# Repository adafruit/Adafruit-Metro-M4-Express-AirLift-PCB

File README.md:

## Adafruit Metro M4 Express AirLift (WiFi) - Lite PCB

<a href="http://www.adafruit.com/products/4000"><br/>
Click here to purchase one from the Adafruit shop</a>

PCB files for the Adafruit Metro M4 Express AirLift (WiFi) - Lite. 

Format is EagleCAD schematic and board layout
* https://www.adafruit.com/product/4000

### Description

Give your next project a lift with _AirLift_ - our witty name for the ESP32 co-processor that graces this Metro M4. You already know about the **Adafruit Metro M4** featuring the **Microchip ATSAMD51**, with it's 120MHz Cortex M4 with floating point support. With a train-load of FLASH and RAM, your code will be fast and roomy. And what better way to improve it than to add wireless? Now cooked in directly on board, you get a certified WiFi module that can handle all your TLS and socket needs, it even has root certificates pre-loaded.

This Metro is the same size as the others, and is compatible with all our shields. It's got analog pins where you expect, and SPI/UART/I2C hardware support in the same spot as the Metro 328 and M0. But! It's powered with an ATSAMD51J19:
 * Cortex M4 core running at **120 MHz**
 * [Floating point support with Cortex M4 DSP instructions](https://developer.arm.com/technologies/dsp/dsp-for-cortex-m)
 * **512 KB** flash, **192 KB** RAM
 * 32-bit, 3.3V logic and power
 * Dual 1 MSPS DAC (A0 and A1)
 * Dual 1 MSPS ADC (8 analog pins)
 * 6 x hardware SERCOM (I2C, SPI or UART)
 * 22 x PWM outputs
 * Stereo I2S input/output with MCK pin
 * 10-bit Parallel capture controller (for camera/video in)
 * Built in crypto engines with AES (256 bit), true RNG, Pubkey controller
 * 64 QFN

Pretty good start right? So we put this chip on a PCB with all these nice extras:
 * **Power the METRO M4** with 7-9V polarity protected DC or the micro USB connector to any 5V USB source. The 2.1mm DC jack has an on/off switch next to it so you can turn off your setup easily. The METRO will automagically switch between USB and DC.
 * **METRO has 25 GPIO** pins, 8 of which are analog in, and two of which is a true analog out. There's a hardware SPI port, hardware I2C port and hardware UART. Logic level is 3.3V
 * **Native USB**, there's no need for a hardware USB to Serial converter as the Metro M4 has built in USB support. When used to act like a serial device, the USB interface can be used by any computer to listen/send data to the METRO, and can also be used to launch and update code via the bootloader. It can also act like an HID keyboard or mouse.
 * **AirLift WiFi Co-processor**, with TLS/SSL support, plenty of RAM for sockets, communication is over SPI and has Arduino and CircuitPython libraries ready to go for fast wireless integration.
 * **Four indicator LEDs and one NeoPixel**, on the back edge of the PCB, for easy debugging. One green power LED, two RX/TX LEDs for data being sent over USB, and a red LED connected. Next to the reset button there is an RGB NeoPixel that can be used for any purpose.
 * **2 MB QSPI Flash** storage chip is included on board. You can use the SPI Flash storage like a very tiny hard drive. When used in Circuit Python, the 2 MB flash acts as storage for all your scripts, libraries and files. When used in Arduino, you can read/write files to it, like a little datalogger or SD card, and then with our helper program, access the files over USB.
 * **Easy reprogramming**, comes pre-loaded with the [UF2 bootloader](https://learn.adafruit.com/adafruit-metro-m0-express-designed-for-circuitpython/uf2-bootloader), which looks like a USB storage key. Simply drag firmware on to program, no special tools or drivers needed! It can be used to load up CircuitPython or Arduino IDE (it is bossa v1.8 compatible)
We have a working Arduino board support package, with lots of stuff working, but our primary target for this board is CircuitPython - with 120 MHz, and 192KB of RAM CircuitPython runs really well on this chip! CircuitPython's built in support for JSON parsing plus our requests compatible library makes it incredibly easy to build secure IoT projects in just a few minutes.

So what are you waiting for? Pick up a Metro M4 AirLift today and be amazed at how easy and fast it is to get started with IoT projects using CircuitPython!

### License

Adafruit invests time and resources providing this open source design, please support Adafruit and open-source hardware by purchasing products from [Adafruit](https://www.adafruit.com)!

Designed by Limor Fried/Ladyada for Adafruit Industries.

Creative Commons Attribution/Share-Alike, all text above must be included in any redistribution. 
See license.txt for additional details.

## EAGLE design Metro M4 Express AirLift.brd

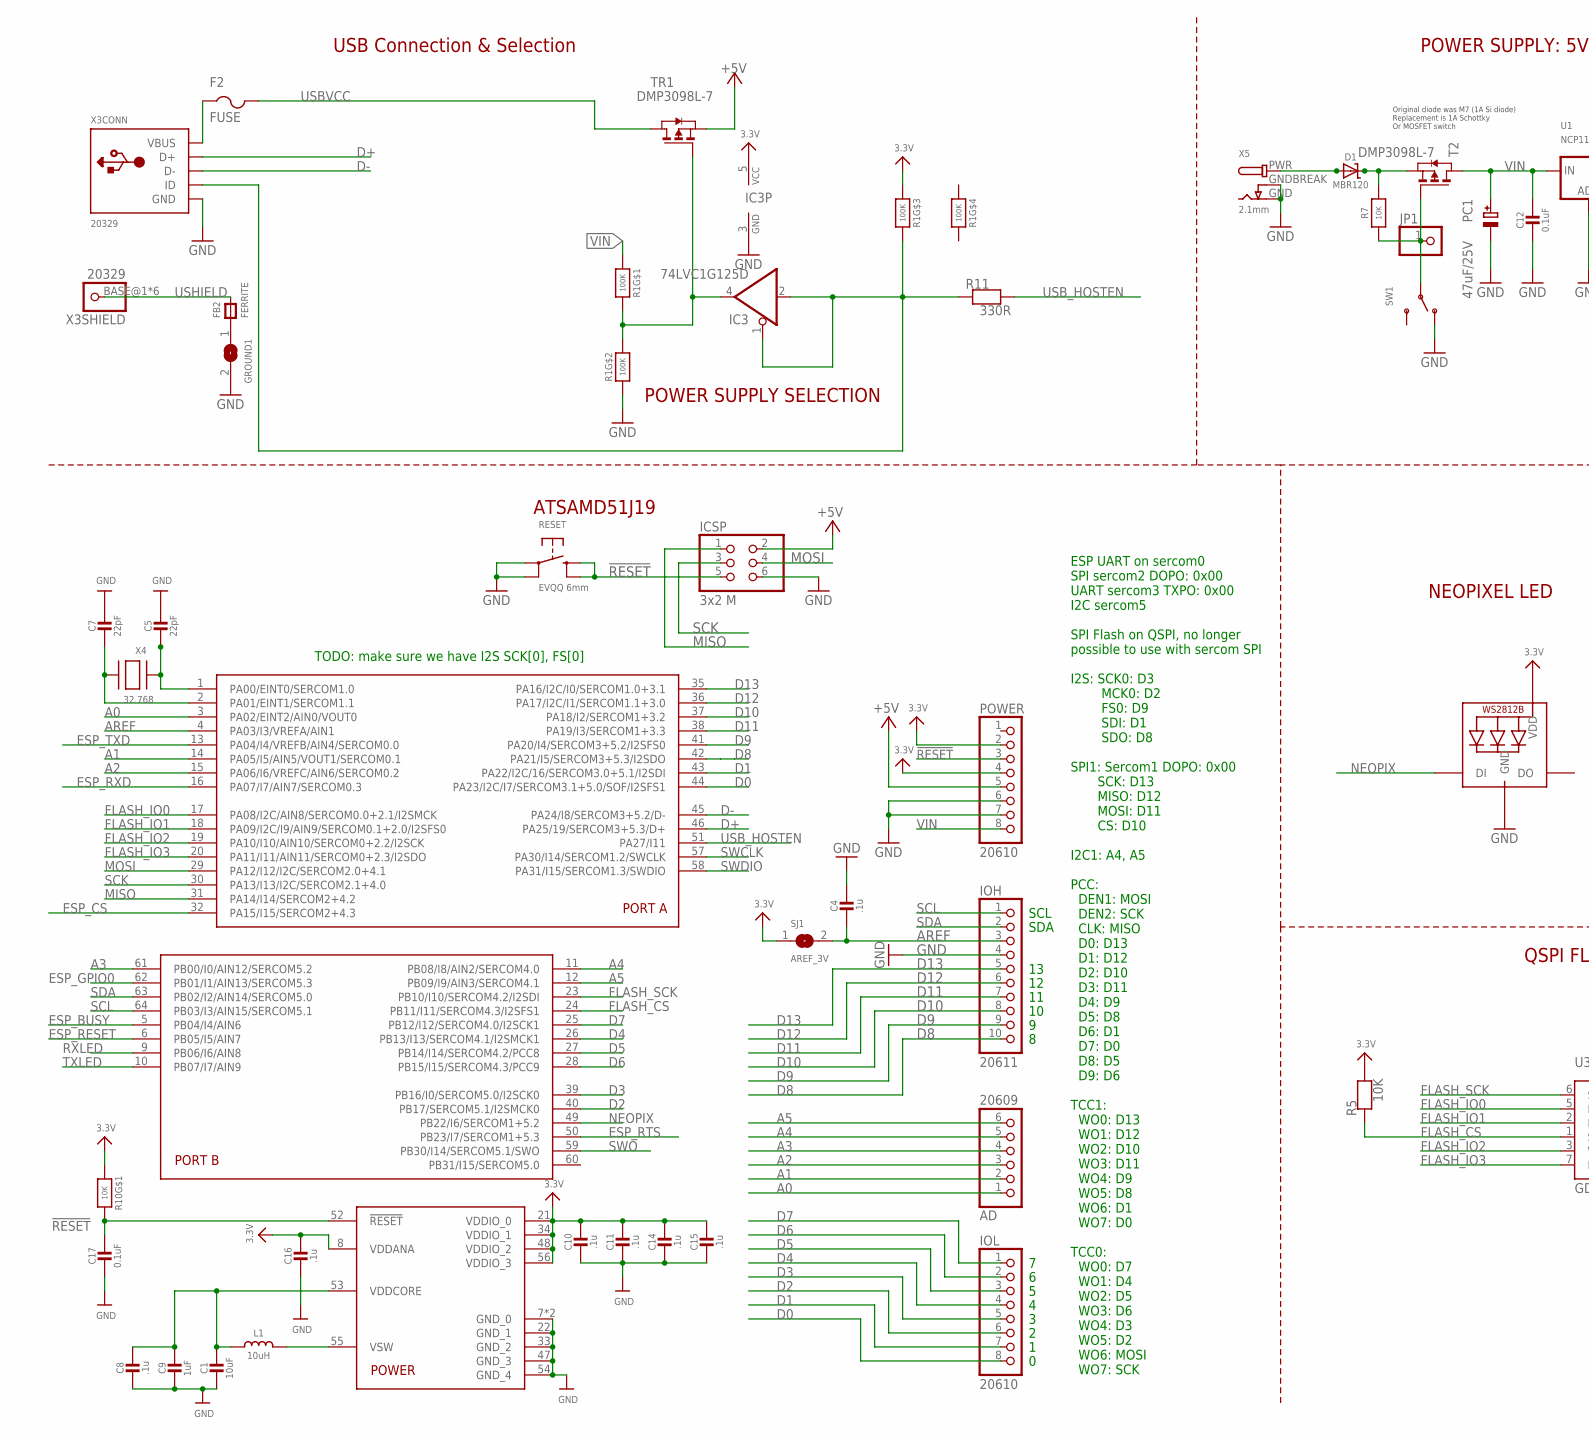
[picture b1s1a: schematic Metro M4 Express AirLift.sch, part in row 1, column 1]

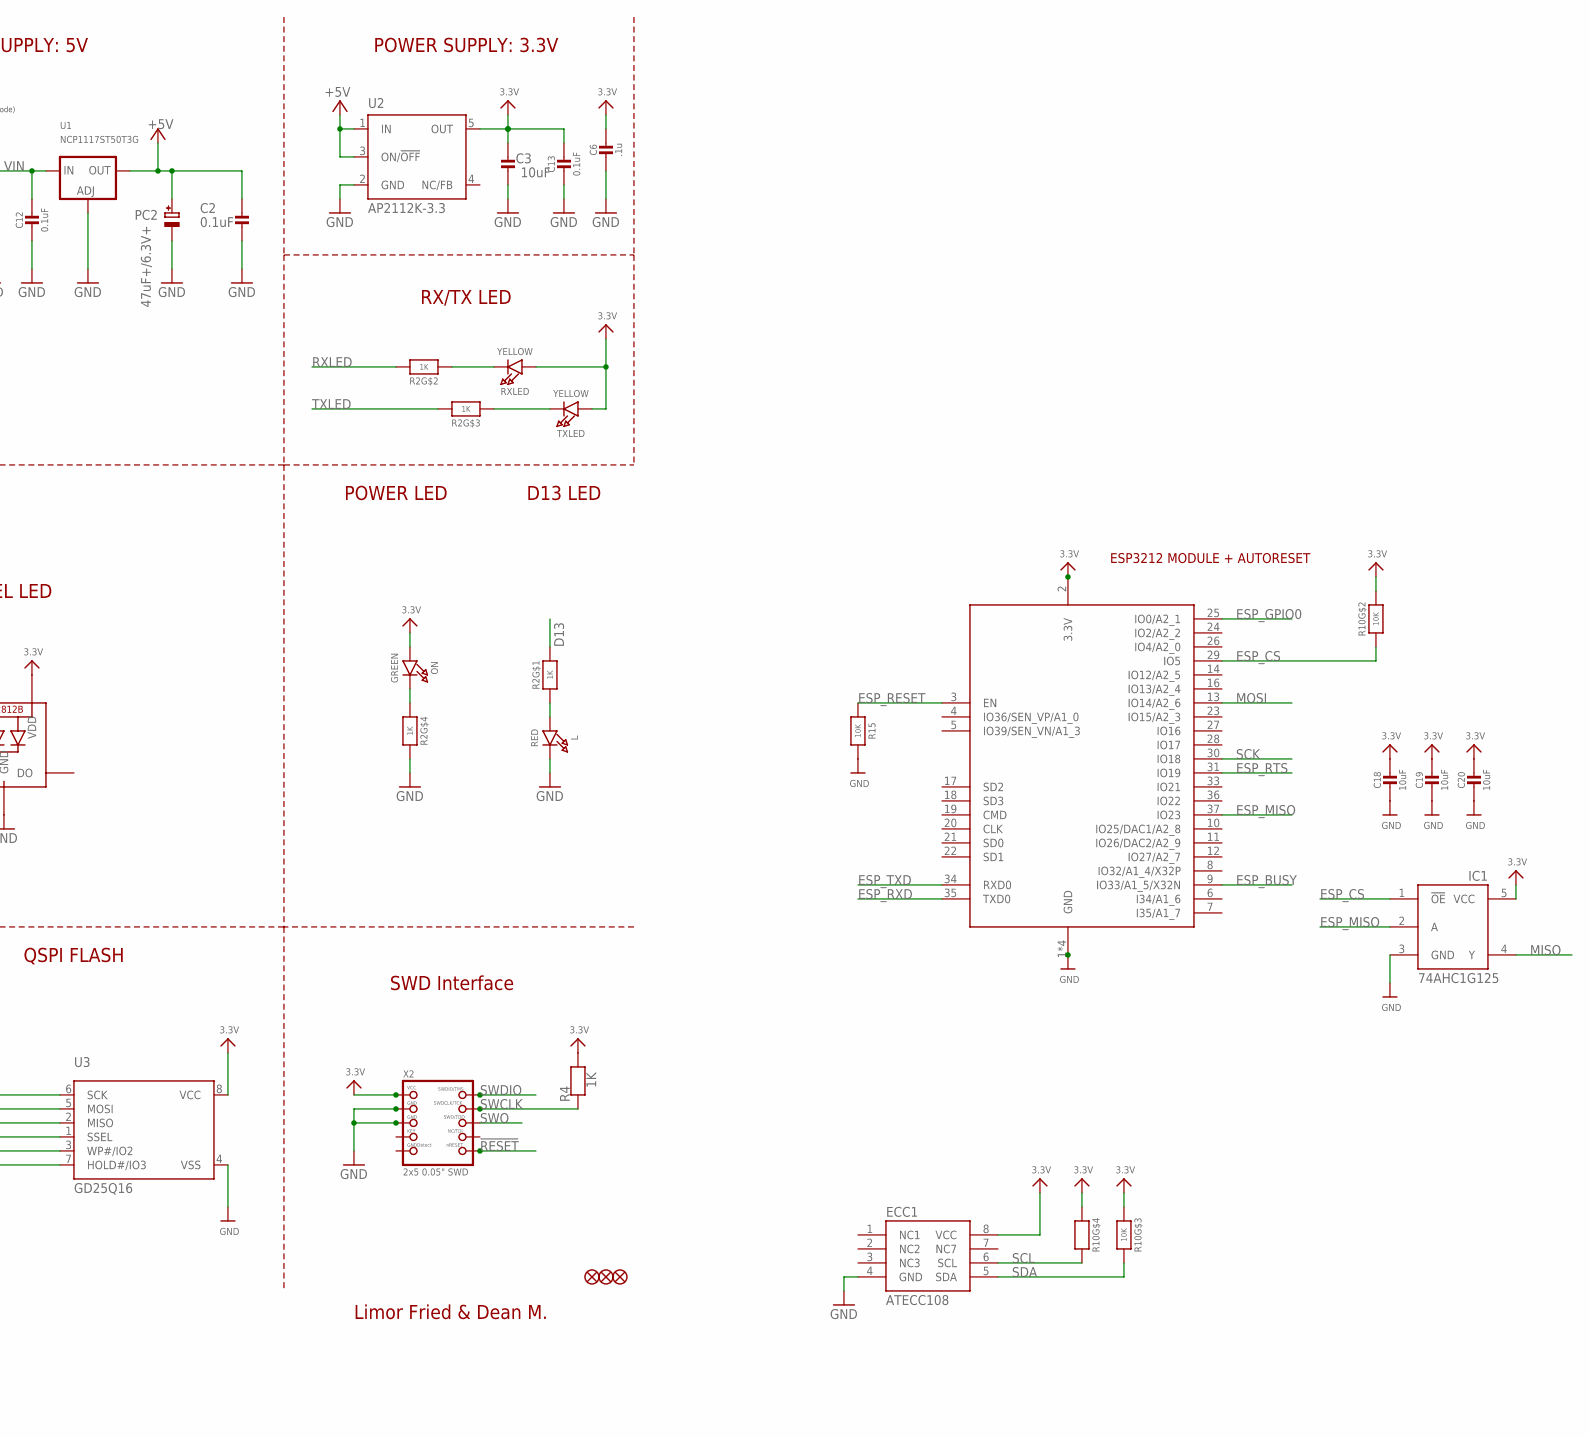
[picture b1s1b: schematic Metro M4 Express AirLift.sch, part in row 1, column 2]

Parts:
AD: 20609; 1X06_OVALWAVE
C1, C3, C18, C19, C20: 10uF; 0805-NO
C2: 0.1uF; 0805-NO
C4, C6, C8, C10, C11, C14, C15, C16: .1u; 0603-NO
C5, C7: 22pF; 0603-NO
C9: 1uF; 0603-NO
C12, C13, C17: 0.1uF; 0603-NO
D1: MBR120; SOD-123
ECC1: ATECC108; SOIC8
F2: FUSE; R1206
FB2: FERRITE; 0805-NO
FD1, FD2, FD3: FIDUCIAL_1MM
GROUND1: SOLDERJUMPERCLOSED; SOLDERJUMPER_CLOSEDWIRE
IC1: 74AHC1G125; SOT23-5L
IC3: 74LVC1G125D; SOT23-5
ICSP: 3x2 M; 2X03_ROUND_70MIL
IOH: 20611; 1X10_OVALWAVE
IOL: 20610; 1X08_OVALWAVE
JP1: HEADER-1X1ROUND; 1X01_ROUND
L: RED; CHIPLED_0805_NOOUTLINE
L1: 10uH; INDUCTOR_1007
LED1: WS2812B3535; LED3535
ON: GREEN; CHIPLED_0805_NOOUTLINE
PC1: 47uF/25V; PANASONIC_D
PC2: 47uF+/6.3V+; PANASONIC_D
POWER: 20610; 1X08_OVALWAVE
R1: 100K; RESPACK_4X0603
R2: 1K; RESPACK_4X0603
R4: 1K; 0603-NO
R5, R7, R15: 10K; 0603-NO
R10: 10K; RESPACK_4X0603
R11: 330R; 0603-NO
RESET: EVQQ 6mm; EVQ-Q2_SMALLER
RXLED: YELLOW; CHIPLED_0805_NOOUTLINE
SJ1: AREF_3V; SOLDERJUMPER_CLOSEDWIRE
SW1: SWITCH_SPDT; SPDT_SMT_SSSS811101
T2: DMP3098L-7; SOT-23
TR1: DMP3098L-7; SOT-23
TXLED: YELLOW; CHIPLED_0805_NOOUTLINE
U1: NCP1117ST50T3G; SOT223-R
U2: AP2112K-3.3; SOT23-DBV
U3: GD25Q16; SOIC8_208MIL
U$1: ATSAMD51J19; PQFN64-1
X2: 2x5 0.05" SWD; 2X05_1.27MM_BOX_POSTS
X3: 20329; 4UCONN_20329_V2
X4: 32.768; XTAL3215
X5: 2.1mm; DCJACK_2MM_PTH
X6: ESP32_WROOM32; WROOM32

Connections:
3.3V: C3.2, C6.2, C10.2, C11.2, C13.1, C14.2, C15.2, C16.2, C18.1, C19.1, C20.1, ECC1.8 (VCC), IC1.5 (VCC), IC3.5 (VCC), LED1.2 (VDD), ON.A, POWER.2, POWER.4, R1.3 (1), R4.2, R5.2, R10.1, R10.3 (1), R10.4 (1), R10.7 (2), RXLED.A, SJ1.1, TXLED.A, U2.5 (OUT), U3.8 (VCC), U$1.8 (VDDANA), U$1.21 (VDDIO_0), U$1.34 (VDDIO_1), U$1.48 (VDDIO_2), U$1.56 (VDDIO_3), X2.1 (VCC), X6.2 (3.3V)
!RESET: C17.2, ICSP.5, POWER.3, R10.8 (2), RESET.B (S), RESET.B' (S1), U$1.52 (!RESET), X2.10 (NRESET)
+5V: C2.2, ICSP.2, PC2.+, POWER.5, TR1.2 (S), U1.2 (OUT), U1.4 (OUT), U2.1 (IN), U2.3 (ON/!OFF)
A0: AD.1, U$1.3 (PA02/EINT2/AIN0/VOUT0)
A1: AD.2, U$1.14 (PA05/I5/AIN5/VOUT1/SERCOM0.1)
A2: AD.3, U$1.15 (PA06/I6/VREFC/AIN6/SERCOM0.2)
A3: AD.4, U$1.61 (PB00/I0/AIN12/SERCOM5.2)
A4: AD.5, U$1.11 (PB08/I8/AIN2/SERCOM4.0)
A5: AD.6, U$1.12 (PB09/I9/AIN3/SERCOM4.1)
AREF: C4.1, IOH.3, SJ1.2, U$1.4 (PA03/I3/VREFA/AIN1)
D0: IOL.8, U$1.44 (PA23/I2C/I7/SERCOM3.1+5.0/SOF/I2SFS1)
D1: IOL.7, U$1.43 (PA22/I2C/16/SERCOM3.0+5.1/I2SDI)
D2: IOL.6, U$1.40 (PB17/SERCOM5.1/I2SMCK0)
D3: IOL.5, U$1.39 (PB16/I0/SERCOM5.0/I2SCK0)
D4: IOL.4, U$1.26 (PB13/I13/SERCOM4.1/I2SMCK1)
D5: IOL.3, U$1.27 (PB14/I14/SERCOM4.2/PCC8)
D6: IOL.2, U$1.28 (PB15/I15/SERCOM4.3/PCC9)
D7: IOL.1, U$1.25 (PB12/I12/SERCOM4.0/I2SCK1)
D8: IOH.10, U$1.42 (PA21/I5/SERCOM3+5.3/I2SDO)
D9: IOH.9, U$1.41 (PA20/I4/SERCOM3+5.2/I2SFS0)
D10: IOH.8, U$1.37 (PA18/I2/SERCOM1+3.2)
D11: IOH.7, U$1.38 (PA19/I3/SERCOM1+3.3)
D12: IOH.6, U$1.36 (PA17/I2C/I1/SERCOM1.1+3.0)
D13: IOH.5, R2.8 (2), U$1.35 (PA16/I2C/I0/SERCOM1.0+3.1)
D+: U$1.46 (PA25/19/SERCOM3+5.3/D+), X3.D+
D-: U$1.45 (PA24/I8/SERCOM3+5.2/D-), X3.D-
ESP_BUSY: U$1.5 (PB04/I4/AIN6), X6.9 (IO33/A1_5/X32N)
ESP_CS: IC1.1 (!OE), R10.2 (1), U$1.32 (PA15/I15/SERCOM2+4.3), X6.29 (IO5)
ESP_GPIO0: U$1.62 (PB01/I1/AIN13/SERCOM5.3), X6.25 (IO0/A2_1)
ESP_MISO: IC1.2 (A), X6.37 (IO23)
ESP_RESET: R15.1, U$1.6 (PB05/I5/AIN7), X6.3 (EN)
ESP_RTS: U$1.50 (PB23/I7/SERCOM1+5.3), X6.31 (IO19)
ESP_RXD: U$1.16 (PA07/I7/AIN7/SERCOM0.3), X6.35 (TXD0)
ESP_TXD: U$1.13 (PA04/I4/VREFB/AIN4/SERCOM0.0), X6.34 (RXD0)
FLASH_CS: R5.1, U3.1 (SSEL), U$1.24 (PB11/I11/SERCOM4.3/I2SFS1)
FLASH_IO0: U3.5 (MOSI), U$1.17 (PA08/I2C/AIN8/SERCOM0.0+2.1/I2SMCK)
FLASH_IO1: U3.2 (MISO), U$1.18 (PA09/I2C/I9/AIN9/SERCOM0.1+2.0/I2SFS0)
FLASH_IO2: U3.3 (WP#/IO2), U$1.19 (PA10/I10/AIN10/SERCOM0+2.2/I2SCK)
FLASH_IO3: U3.7 (HOLD#/IO3), U$1.20 (PA11/I11/AIN11/SERCOM0+2.3/I2SDO)
FLASH_SCK: U3.6 (SCK), U$1.23 (PB10/I10/SERCOM4.2/I2SDI)
GND: C1.2, C2.1, C3.1, C4.2, C5.2, C6.1, C7.2, C8.1, C9.2, C10.1, C11.1, C12.2, C13.2, C14.1, C15.1, C16.1, C17.1, C18.2, C19.2, C20.2, ECC1.4 (GND), GROUND1.2, IC1.3 (GND), IC3.3 (GND), ICSP.6, IOH.4, L.C, LED1.4 (GND), PC1.-, PC2.-, POWER.6, POWER.7, R1.2 (1), R2.5 (2), R15.2, RESET.A, RESET.A' (P1), SW1.A (O), U1.1 (ADJ), U2.2 (GND), U3.4 (VSS), U$1.7 (GND_0), U$1.22 (GND_1), U$1.33 (GND_2), U$1.47 (GND_3), U$1.54 (GND_4), U$1.EXP (GND_0), X2.3 (GND), X2.5 (GND), X3.GND, X5.GND, X5.GNDBREAK, X6.1 (GND), X6.15 (GND), X6.38 (GND), X6.P$1 (GND)
MISO: IC1.4 (Y), ICSP.1, U$1.31 (PA14/I14/SERCOM2+4.2)
MOSI: ICSP.4, U$1.29 (PA12/I12/I2C/SERCOM2.0+4.1), X6.13 (IO14/A2_6)
unnamed: L.A, R2.1
unnamed: FB2.1, GROUND1.1
unnamed: ON.C, R2.4 (1)
unnamed: L1.P$2 (2), U$1.55 (VSW)
unnamed: R2.2 (1), RXLED.C
unnamed: R2.3 (1), TXLED.C
unnamed: C5.1, U$1.1 (PA00/EINT0/SERCOM1.0), X4.P$1
unnamed: IC3.1 (OE), IC3.2 (I), R1.6 (2), R11.1, X3.ID
unnamed: IC3.4 (O), R1.7 (2), R1.8 (2), TR1.3 (G)
unnamed: C7.1, U$1.2 (PA01/EINT1/SERCOM1.1), X4.P$2
unnamed: D1.C, R7.2, T2.2 (S)
NEOPIX: LED1.1 (DI), U$1.49 (PB22/I6/SERCOM1+5.2)
PWRIN: D1.A, X5.PWR
PWR_SWITCH: JP1.1, R7.1, SW1.B, T2.3 (G)
RXLED: R2.7 (2), U$1.9 (PB06/I6/AIN8)
SCK: ICSP.3, U$1.30 (PA13/I13/I2C/SERCOM2.1+4.0), X6.30 (IO18)
SCL: ECC1.6 (SCL), IOH.1, R10.5 (2), U$1.64 (PB03/I3/AIN15/SERCOM5.1)
SDA: ECC1.5 (SDA), IOH.2, R10.6 (2), U$1.63 (PB02/I2/AIN14/SERCOM5.0)
SWCLK: R4.1, U$1.57 (PA30/I14/SERCOM1.2/SWCLK), X2.4 (SWDCLK)
SWDIO: U$1.58 (PA31/I15/SERCOM1.3/SWDIO), X2.2 (SWDIO)
SWO: U$1.59 (PB30/I14/SERCOM5.1/SWO), X2.6 (SWO)
TXLED: R2.6 (2), U$1.10 (PB07/I7/AIN9)
USBVCC: F2.2, TR1.1 (D)
USB_HOSTEN: R11.2, U$1.51 (PA27/I11)
USHIELD: FB2.2, X3.BASE@1 (1), X3.BASE@2 (1), X3.SPRT@1 (1), X3.SPRT@2 (1), X3.SPRT@3 (1), X3.SPRT@4 (1)
VBUS: F2.1, X3.VBUS
VDDCORE: C1.1, C8.2, C9.1, L1.P$1 (1), U$1.53 (VDDCORE)
VIN: C12.1, PC1.+, POWER.8, R1.1, T2.1 (D), U1.3 (IN)

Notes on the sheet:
SDA
SCL
Limor Fried & Dean M.
Original diode was M7 (1A Si diode) Replacement is 1A Schottky Or MOSFET switch
POWER SUPPLY: 5V
USB Connection & Selection
POWER SUPPLY: 3.3V
POWER LED
ATSAMD51J19
POWER SUPPLY SELECTION
D13 LED
RX/TX LED
NEOPIXEL LED
QSPI FLASH
SWD Interface
ESP UART on sercom0 SPI sercom2 DOPO: 0x00 UART sercom3 TXPO: 0x00 I2C sercom5 SPI Flash on QSPI, no longer possible to use with sercom SPI I2S: SCK0: D3 MCK0: D2 FS0: D9 SDI: D1 SDO: D8 SPI1: Sercom1 DOPO: 0x00 SCK: D13 MISO: D12 MOSI: D11 CS: D10 I2C1: A4, A5 PCC: DEN1: MOSI DEN2: SCK CLK: MISO D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
TODO: make sure we have I2S SCK[0], FS[0]
ESP3212 MODULE + AUTORESET

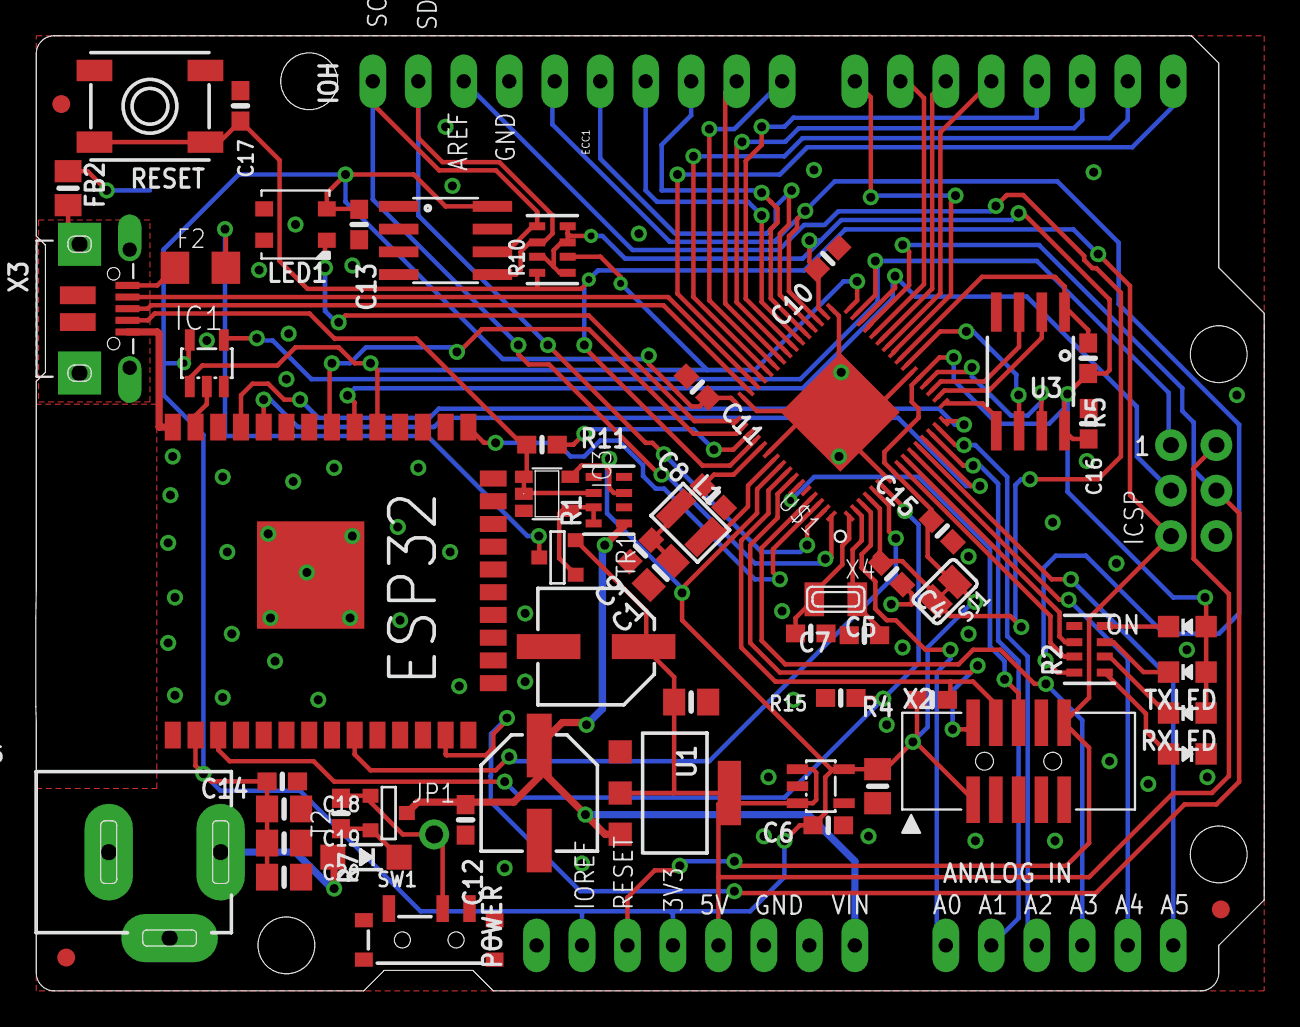
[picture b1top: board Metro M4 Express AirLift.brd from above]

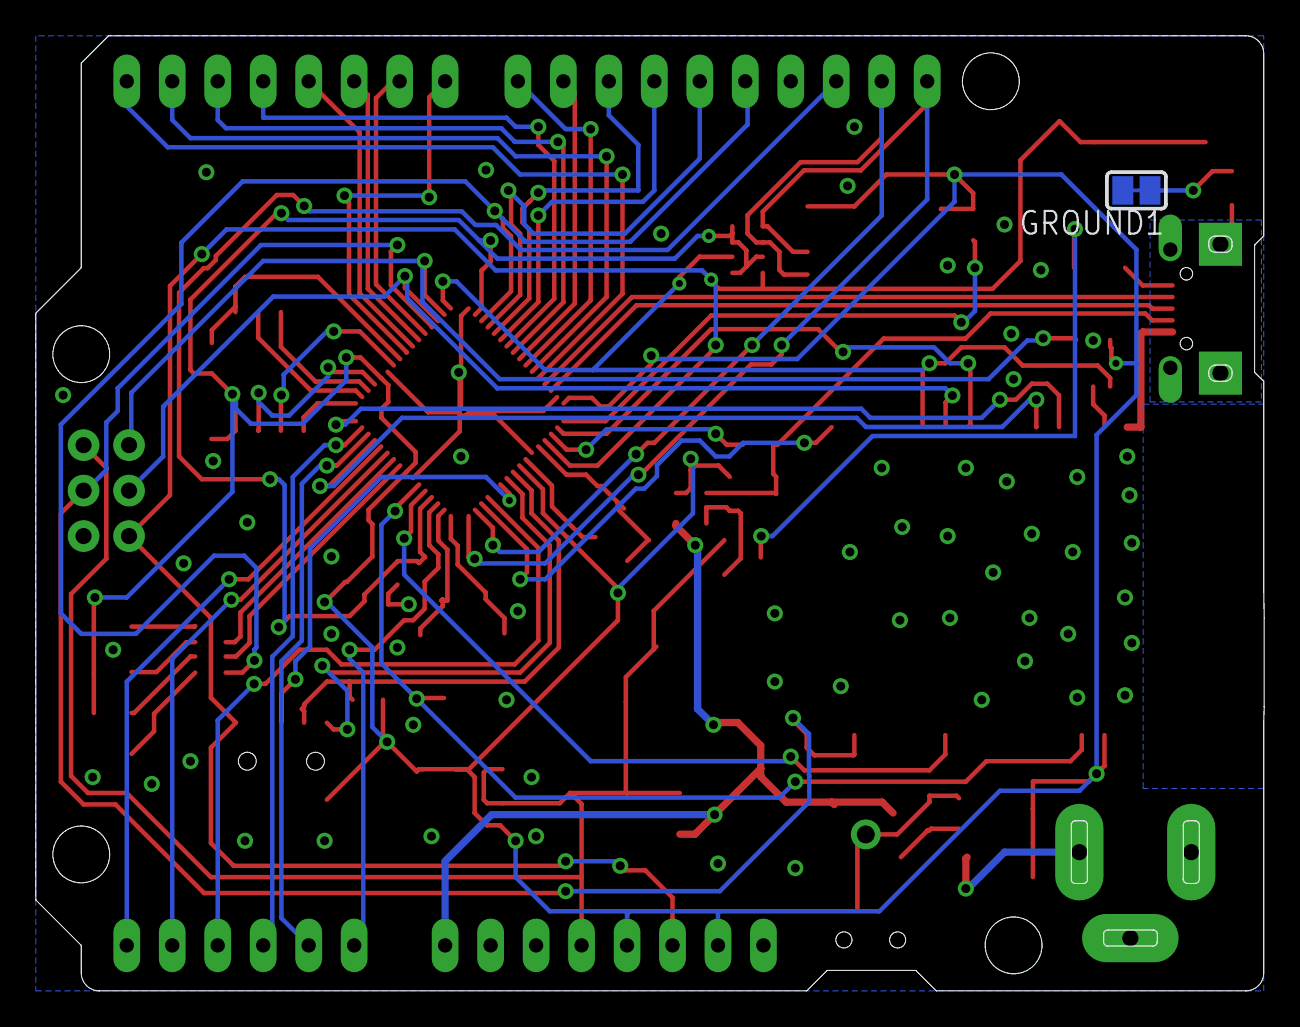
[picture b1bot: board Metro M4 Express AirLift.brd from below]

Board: 2 copper layers, 68.6 x 53.3 mm, 68 parts (2 on the bottom side), 71 nets.

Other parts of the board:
U$27: METROM4_AIRLIFT_LITE_BOT
U$39: METROM4_AIRLIFT_LITE_TOP

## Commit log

2019-04-23 Add board files
2019-07-17 updated to use cookiecutter for pcb repos
2022-05-02 Added Prettypins

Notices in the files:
parts and their libraries:
microbuilder: This work is placed in the public domain, and may be freely used for commercial and non-commercial work with the following conditions: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
SparkFun-Aesthetics: Licensing: CC v3.0 Share-Alike You are welcome to use this library for commercial purposes.
